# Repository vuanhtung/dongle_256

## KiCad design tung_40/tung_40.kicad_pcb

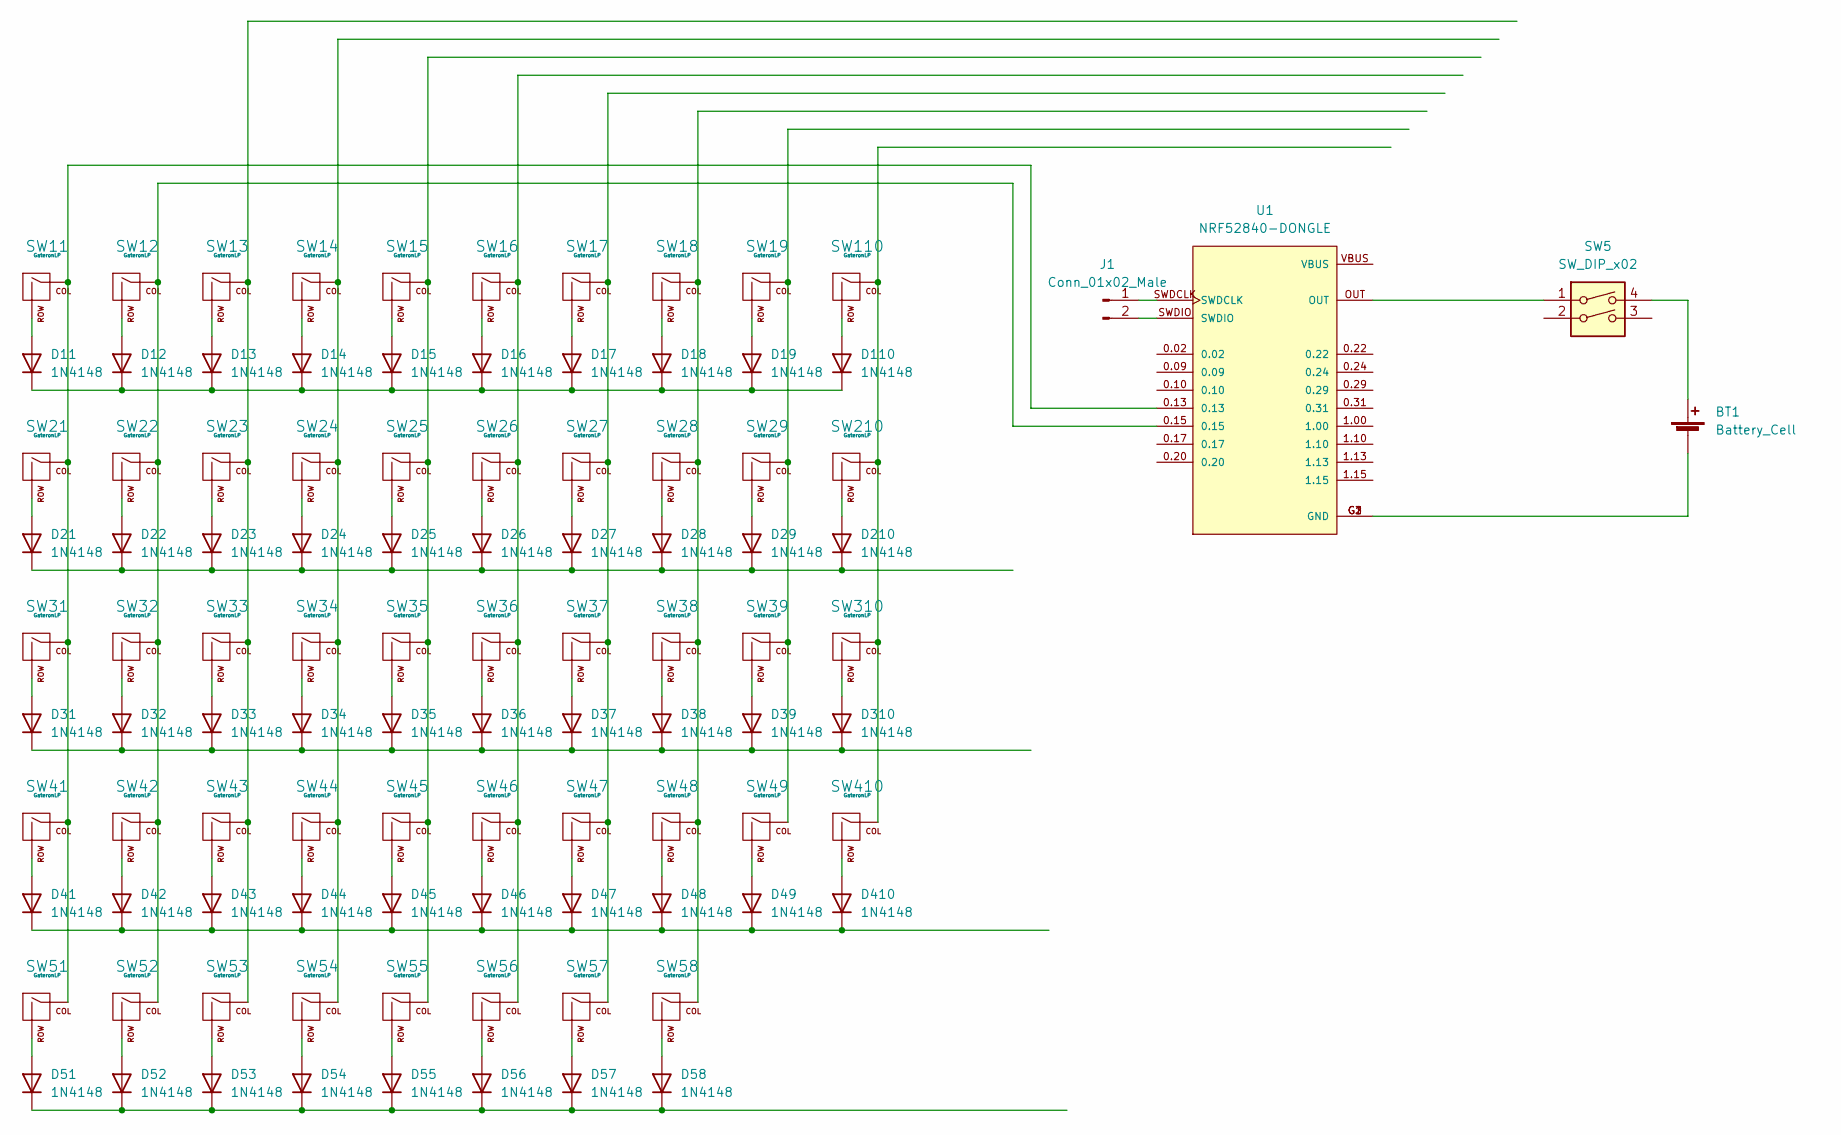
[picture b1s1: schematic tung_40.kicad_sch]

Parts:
BT1: Battery_Cell; TBH-CR2032-M04
D11, D12, D13, D14, D15, D16, D17, D18, D19, D21, D22, D23, D24, D25, D26, D27, D28, D29, D31, D32, D33, D34, D35, D36, D37, D38, D39, D41, D42, D43, D44, D45, D46, D47, D48, D49, D51, D52, D53, D54, D55, D56, D57, D58, D110, D210, D310, D410: 1N4148; D_DO-35_SOD27_P7.62mm_Horizontal
J1: Conn_01x02_Male; PinHeader_1x02_P2.54mm_Vertical
SW5: SW_DIP_x02; SW_DIP_SPSTx02_Slide_9.78x7.26mm_W7.62mm_P2.54mm
SW11, SW12, SW13, SW14, SW15, SW16, SW17, SW18, SW19, SW21, SW22, SW23, SW24, SW25, SW26, SW27, SW28, SW29, SW31, SW32, SW33, SW34, SW35, SW36, SW37, SW38, SW39, SW41, SW42, SW43, SW44, SW45, SW46, SW47, SW48, SW49, SW51, SW52, SW53, SW54, SW55, SW56, SW57, SW58, SW110, SW210, SW310, SW410: GateronLP; SW_Gateron_LO_PRO_1.00u_NO_LED_REVERSABLE_PCB
U1: NRF52840-DONGLE; MODULE_NRF52840-DONGLE; PARTREV 1.1

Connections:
unnamed: BT1.1 (+), SW5.4
unnamed: BT1.2 (-), U1.G1 (GND), U1.G2 (GND), U1.G3 (GND)
unnamed: D11.1 (K), D12.1 (K), D13.1 (K), D14.1 (K), D15.1 (K), D16.1 (K), D17.1 (K), D18.1 (K), D19.1 (K), D110.1 (K)
unnamed: D11.2 (A), SW11.2 (ROW)
unnamed: D12.2 (A), SW12.2 (ROW)
unnamed: D13.2 (A), SW13.2 (ROW)
unnamed: D14.2 (A), SW14.2 (ROW)
unnamed: D15.2 (A), SW15.2 (ROW)
unnamed: D16.2 (A), SW16.2 (ROW)
unnamed: D17.2 (A), SW17.2 (ROW)
unnamed: D18.2 (A), SW18.2 (ROW)
unnamed: D19.2 (A), SW19.2 (ROW)
unnamed: D21.1 (K), D22.1 (K), D23.1 (K), D24.1 (K), D25.1 (K), D26.1 (K), D27.1 (K), D28.1 (K), D29.1 (K), D210.1 (K)
unnamed: D21.2 (A), SW21.2 (ROW)
unnamed: D22.2 (A), SW22.2 (ROW)
unnamed: D23.2 (A), SW23.2 (ROW)
unnamed: D24.2 (A), SW24.2 (ROW)
unnamed: D25.2 (A), SW25.2 (ROW)
unnamed: D26.2 (A), SW26.2 (ROW)
unnamed: D27.2 (A), SW27.2 (ROW)
unnamed: D28.2 (A), SW28.2 (ROW)
unnamed: D29.2 (A), SW29.2 (ROW)
unnamed: D31.1 (K), D32.1 (K), D33.1 (K), D34.1 (K), D35.1 (K), D36.1 (K), D37.1 (K), D38.1 (K), D39.1 (K), D310.1 (K)
unnamed: D31.2 (A), SW31.2 (ROW)
unnamed: D32.2 (A), SW32.2 (ROW)
unnamed: D33.2 (A), SW33.2 (ROW)
unnamed: D34.2 (A), SW34.2 (ROW)
unnamed: D35.2 (A), SW35.2 (ROW)
unnamed: D36.2 (A), SW36.2 (ROW)
unnamed: D37.2 (A), SW37.2 (ROW)
unnamed: D38.2 (A), SW38.2 (ROW)
unnamed: D39.2 (A), SW39.2 (ROW)
unnamed: D41.1 (K), D42.1 (K), D43.1 (K), D44.1 (K), D45.1 (K), D46.1 (K), D47.1 (K), D48.1 (K), D49.1 (K), D410.1 (K)
unnamed: D41.2 (A), SW41.2 (ROW)
unnamed: D42.2 (A), SW42.2 (ROW)
unnamed: D43.2 (A), SW43.2 (ROW)
unnamed: D44.2 (A), SW44.2 (ROW)
unnamed: D45.2 (A), SW45.2 (ROW)
unnamed: D46.2 (A), SW46.2 (ROW)
unnamed: D47.2 (A), SW47.2 (ROW)
unnamed: D48.2 (A), SW48.2 (ROW)
unnamed: D49.2 (A), SW49.2 (ROW)
unnamed: D51.1 (K), D52.1 (K), D53.1 (K), D54.1 (K), D55.1 (K), D56.1 (K), D57.1 (K), D58.1 (K)
unnamed: D51.2 (A), SW51.2 (ROW)
unnamed: D52.2 (A), SW52.2 (ROW)
unnamed: D53.2 (A), SW53.2 (ROW)
unnamed: D54.2 (A), SW54.2 (ROW)
unnamed: D55.2 (A), SW55.2 (ROW)
unnamed: D56.2 (A), SW56.2 (ROW)
unnamed: D57.2 (A), SW57.2 (ROW)
unnamed: D58.2 (A), SW58.2 (ROW)
unnamed: D110.2 (A), SW110.2 (ROW)
unnamed: D210.2 (A), SW210.2 (ROW)
unnamed: D310.2 (A), SW310.2 (ROW)
unnamed: D410.2 (A), SW410.2 (ROW)
unnamed: J1.1, U1.SWDCLK
unnamed: J1.2, U1.SWDIO
unnamed: SW5.1, U1.OUT
unnamed: SW11.1 (COL), SW21.1 (COL), SW31.1 (COL), SW41.1 (COL), SW51.1 (COL), U1.0.13
unnamed: SW12.1 (COL), SW22.1 (COL), SW32.1 (COL), SW42.1 (COL), SW52.1 (COL), U1.0.15
unnamed: SW13.1 (COL), SW23.1 (COL), SW33.1 (COL), SW43.1 (COL), SW53.1 (COL)
unnamed: SW14.1 (COL), SW24.1 (COL), SW34.1 (COL), SW44.1 (COL), SW54.1 (COL)
unnamed: SW15.1 (COL), SW25.1 (COL), SW35.1 (COL), SW45.1 (COL), SW55.1 (COL)
unnamed: SW16.1 (COL), SW26.1 (COL), SW36.1 (COL), SW46.1 (COL), SW56.1 (COL)
unnamed: SW17.1 (COL), SW27.1 (COL), SW37.1 (COL), SW47.1 (COL), SW57.1 (COL)
unnamed: SW18.1 (COL), SW28.1 (COL), SW38.1 (COL), SW48.1 (COL), SW58.1 (COL)
unnamed: SW19.1 (COL), SW29.1 (COL), SW39.1 (COL), SW49.1 (COL)
unnamed: SW110.1 (COL), SW210.1 (COL), SW310.1 (COL), SW410.1 (COL)

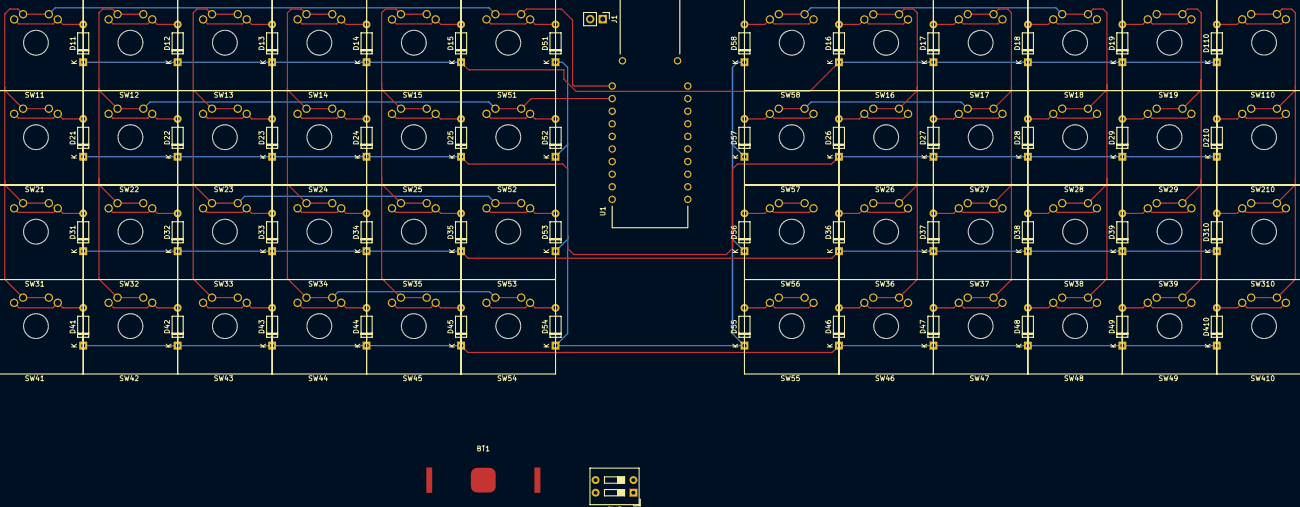
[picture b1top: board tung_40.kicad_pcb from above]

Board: 2 copper layers, 100 parts (0 on the bottom side), 68 nets.

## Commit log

2023-01-07 start tung_40
2023-01-07 48 keys in progress
2023-04-08 continue 48 keys
